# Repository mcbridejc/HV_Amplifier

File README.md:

High Voltage Amplifier
======================

A high-voltage amplifier takes a lower voltage input signal -- e.g. from a 
function generator of some sort -- and amplifies it to a high voltage. In this
case, the output range is -200V to +200V. High voltage amplifiers can be used
for a variety of applications, such as driving piezos, or digital microfluidics
electrodes. 

This board was created in KiCad 6.0.4. 

## A WARNING

This project can be dangerous. 200V is sufficient to kill you under
the right conditions. Even under the best conditions, it can give you a 
painful shock. You should not build this unless you know what you're doing.
If you do build this, you should handle it with caution. Be very careful about
what you touch when it is energized. Don't touch it with both hands
simultaneously. If you don't have to have it exposed, enclose it. Insulate
any wiring connected to the HV output.

## Description

This design uses the Apex PA88 high-voltage op-amp. These are fairly expensive
(~$250) at mouser, but I was able to find one for much cheaper on Ebay when I
built this. It also has a switching power supply which generates the positive
and negative high voltage rails from a 9V input. 

It can be operated at 100V, or 200V, based on whether the jumper JP1 is shorted.

The gain (Output voltage / control voltage) is adjustable from 15.9x to 60.2x,
using the potentiometer. At maximum gain, an input of 3.3V will provide an
output of 199V. 

When idle, it draws about 40mA when operating at 100V, and about 80mA at 200V. It
should be able to source about 4mA, although I have not tested under this kind
of load. For my application the current draw is much less. At some point I may
stress test it, but I am putting it off in case this test proves to be destructive!

## Enclosure 

I have provided some mesh files for a 3D printable enclosure. It requires some
M3 heat inserts (like [these](https://www.amazon.com/initeq-M3-0-5-Threaded-Inserts-Printing/dp/B073W2898C/))
and 18-23mm long M3 screws (like [these](https://www.amazon.com/M3-0-5-Stainless-Socket-Screws-Coverage/dp/B09B3992F4/)) 
to assemble. The STLs can be found in the [enclosure](enclosure/) directory.

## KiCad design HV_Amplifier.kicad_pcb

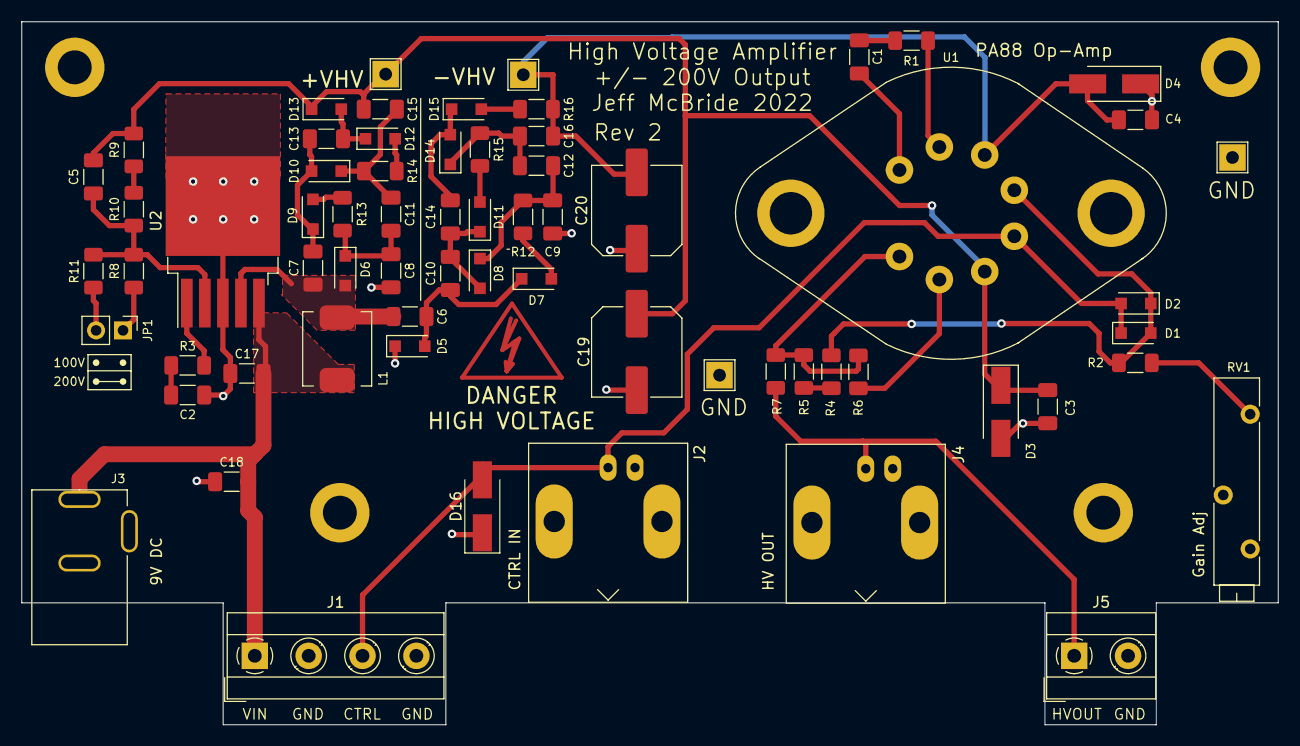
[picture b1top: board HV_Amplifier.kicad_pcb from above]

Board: 2 copper layers, 118.5 x 66.3 mm, 70 parts (0 on the bottom side), 34 nets.

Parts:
C1: 15pF; C_1206_3216Metric_Pad1.33x1.80mm_HandSolder
C2: 1u; C_1206_3216Metric_Pad1.33x1.80mm_HandSolder
C3, C4: 0.1u; C_1206_3216Metric_Pad1.33x1.80mm_HandSolder
C5: DNP; C_1206_3216Metric_Pad1.33x1.80mm_HandSolder
C6, C7, C8, C9, C10, C11, C12, C13, C14, C15, C16: 0.22u; C_1206_3216Metric_Pad1.33x1.80mm_HandSolder
C17, C18: 10u; C_1206_3216Metric_Pad1.33x1.80mm_HandSolder
C19, C20: 1.8u; C_Elec_8x10.2
D1, D2, D5, D6, D7, D8, D9, D10, D11, D12, D13, D14, D15: DSS120U; D_SOD-123F
D3, D4: SMAJ200A; D_SMA_Handsoldering
D16: SMA6J5.0CA; D_SMA_Handsoldering
H1, H2, H3, H4: MountingHole_Pad; MountingHole_3.2mm_M3_DIN965_Pad
J1: CTRL_TERM; TerminalBlock_MetzConnect_Type101_RT01604HBWC_1x04_P5.08mm_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
J2, J4: BNC; BNC_Amphenol_B6252HB-NPP3G-50_Horizontal
J3: Barrel_Jack_Switch; PJ-202AH
J5: Screw_Terminal_01x02; TerminalBlock_MetzConnect_Type101_RT01602HBWC_1x02_P5.08mm_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
JP1: 100/200V SEL; PinHeader_1x02_P2.54mm_Vertical
L1: 68uH; Inductor_SPM6545_7x6.5
R1, R7: 100; R_1206_3216Metric_Pad1.30x1.75mm_HandSolder
R2: 16.9k; R_1206_3216Metric_Pad1.30x1.75mm_HandSolder
R3: 1k; R_1206_3216Metric_Pad1.30x1.75mm_HandSolder
R4, R5, R9, R10: 499k; R_1206_3216Metric_Pad1.30x1.75mm_HandSolder
R6: 150; R_1206_3216Metric_Pad1.30x1.75mm_HandSolder
R8, R11: 12.4k; R_1206_3216Metric_Pad1.30x1.75mm_HandSolder
R12, R13, R14, R15, R16: 10; R_1206_3216Metric_Pad1.30x1.75mm_HandSolder
RV1: 50k; Potentiometer_Bourns_3005_Horizontal
TP1: +VHV; TestPoint_THTPad_2.5x2.5mm_Drill1.2mm
TP2: -VHV; TestPoint_THTPad_2.5x2.5mm_Drill1.2mm
TP3, TP4: GND; TestPoint_THTPad_2.5x2.5mm_Drill1.2mm
U1: PA88; TO-3-8
U2: LT117xHV; TO-263-5_TabPin3

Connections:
+VHV: C3.1, C5.2, C15.2, C19.1, D3.1 (K), D13.1 (K), R9.2, TP1.1, U1.3 (+VS)
-VHV: C4.1, C16.2, C20.2, D4.2 (A), R16.2, TP2.1, U1.6 (-VS)
/CTRL: D1.1 (K), D2.2 (A), D16.2 (A2), J1.3, J2.1 (In), U1.4 (+IN)
/FB: C5.1, R8.2, R10.1, R11.2, U2.2 (FB)
/HVOUT: J4.1 (In), J5.1, R7.1
/SW: C6.1, C7.2, D6.2 (A), L1.2, U2.4 (VSW)
/VC: R3.2, U2.1 (VC)
/VIN: C17.2, C18.2, J1.1, J3.1, L1.1, U2.5 (VIN)
GND: C2.1, C3.2, C4.2, C8.1, C9.1, C17.1, C18.1, C19.2, C20.1, D3.2 (A), D4.1 (K), D5.1 (K), D16.1 (A1), H1.1, H2.1, H3.1, H4.1, J1.2, J1.4, J2.2 (Ext), J3.2, J3.3, J4.2 (Ext), J5.2, JP1.1 (A), R8.1, RV1.2, TP3.1, TP4.1, U2.3 (GND)
unnamed: C1.1, R1.1
unnamed: C1.2, U1.8 (CC)
unnamed: C2.2, R3.1
unnamed: C6.2, C10.1, D5.2 (A), D7.1 (K)
unnamed: C10.2, C14.1, D8.2 (A), D11.1 (K)
unnamed: C8.2, C11.1, D6.1 (K), R13.2
unnamed: C11.2, C15.1, D10.1 (K), R14.2
unnamed: C9.2, C12.1, D8.1 (K), R12.2
unnamed: C12.2, C16.1, D14.1 (K), R15.2
unnamed: C13.1, D12.1 (K), D13.2 (A)
unnamed: C7.1, C13.2, D9.1 (K), D10.2 (A)
unnamed: C14.2, D14.2 (A), D15.1 (K)
unnamed: D1.2 (A), D2.1 (K), R2.1, R4.2, U1.5 (-IN)
unnamed: D7.2 (A), R12.1
unnamed: D9.2 (A), R13.1
unnamed: D11.2 (A), R15.1
unnamed: D12.2 (A), R14.1
unnamed: D15.2 (A), R16.1
unnamed: JP1.2 (B), R11.1
unnamed: R1.2, U1.7 (RC)
unnamed: R2.2, RV1.1
unnamed: R4.1, R5.2
unnamed: R5.1, R6.1, R7.2, U1.1 (OUT)
unnamed: R6.2, U1.2 (CL)
unnamed: R9.1, R10.2

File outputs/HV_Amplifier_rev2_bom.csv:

Component,References,Value,Mfg Part Number,Package,Part Description,Voltage,Quantity Per PCB
1,C3-C4,0.1u,,1206,CAP CER 0.1UF 450V X7T 1206,450V,2
2,C6-C16,0.22u,,1206,CAP CER 0.22UF 100V X7R 1206,100V,11
3,C19-C20,1.8u,UUB2G1R8MNL1GS,,,400V,2
4,C17-C18,10u,,1206,CAP CER 10UF 25V X5R 1206,25V,2
5,C1,15pF,,1206,CAP CER 15PF 50V C0G/NP0 1206,50V,1
6,C2,1u,,1206,CAP CER 1UF 16V X7R 1206,16V,1
7,D1-D2 D5-D15,DSS120U,DSS120U,SOD-123F,SCHOTTKY 200V SOD-123FL,,13
8,D16,SMA6J5.0CA,SMA6J5.0CA,SMA,TVS DIODE 5VWM 9.2VC DO214AC TR,,1
9,D3-D4,SMAJ200A,SMAJ200A-TP,SMA,TVS DIODE 200V 324V DO214AC,,2
10,J2 J4,BNC,RF1-01K-D-00-50-BK-HDW,,BNC RA PCB 50 4GHZ ZINC BODY NI,,2
11,J3,Barrel_Jack_Switch,PJ-202AH,,CONN PWR JACK 2X5.5MM KINKED PIN,,1
12,J1,CTRL_TERM,31101104,,TERM BLK 4P SIDE ENT 5.08MM PCB,,1
13,J5,Screw_Terminal_01x02,31101102,,TERM BLK 2P SIDE ENT 5.08MM PCB,,1
14,JP1,100/200V SEL,,,,,1
15,L1,68uH,SPM6545VT-680M-D,,FIXED IND 68UH 1.7A 340 MOHM SMD,,1
16,R12-R16,10,,1206,RES 10 OHM 1% 1/4W 1206,,5
17,R1 R7,100,,1206,RES SMD 100 OHM 1% 1/4W 1206,,2
18,R8 R11,12.4k,,1206,RES 12.4K OHM 1% 1/4W 1206,,2
19,R6,150,,1206,RES 150 OHM 1% 1/2W 1206,,1
20,R2,16.9k,,1206,RES SMD 16.9K OHM 1% 1/4W 1206,,1
21,R3,1k,,1206,RES 1K OHM 1% 1/2W 1206,,1
22,R4-R5 R9-R10,499k,,1206,RES 499K OHM 1% 1/4W 1206,,4
23,RV1,50k,CT20EP503,,TRIMMER 50K OHM 0.5W PC PIN SIDE,,1
24,U2,LT117xHV,LT1171HVCQ,,IC REG MULTI CONFG ADJ 5DDPAK,,1
25,U1,PA88,,TO-3-8,,,1





Component Groups:,26
Component Count:,62
Fitted Components:,61
Number of PCBs:,1
Total components:,61
Schematic Version:,2
Schematic Date:,2022-05-06
PCB Variant:,[u'default']
BoM Date:,Fri 06 May 2022 05:38:52 PM PDT
Schematic Source:,HV_Amplifier.kicad_sch
KiCad Version:,Eeschema 6.0.4-6f826c9f35~116~ubuntu21.10.1

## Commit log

2022-05-07 Commit rev 2 of the board, which fixes a few issues from rev 1:
    - Change to SMD regulator footprint
    - Correct capacitor polarity on C19/C20
    - Flip pins on PA88 (so you can mount it on the top, as intended)
2022-05-07 Add README and enclosure models
2022-05-08 Add LTSpice circuit
2022-05-08 Create LICENSE
